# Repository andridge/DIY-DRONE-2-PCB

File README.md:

# DIY-DRONE-PCB

https://github.com/andridge/DIY-DRONE-PCB/assets/46260701/71bfbc1b-cc14-4874-8b07-093efc903e75

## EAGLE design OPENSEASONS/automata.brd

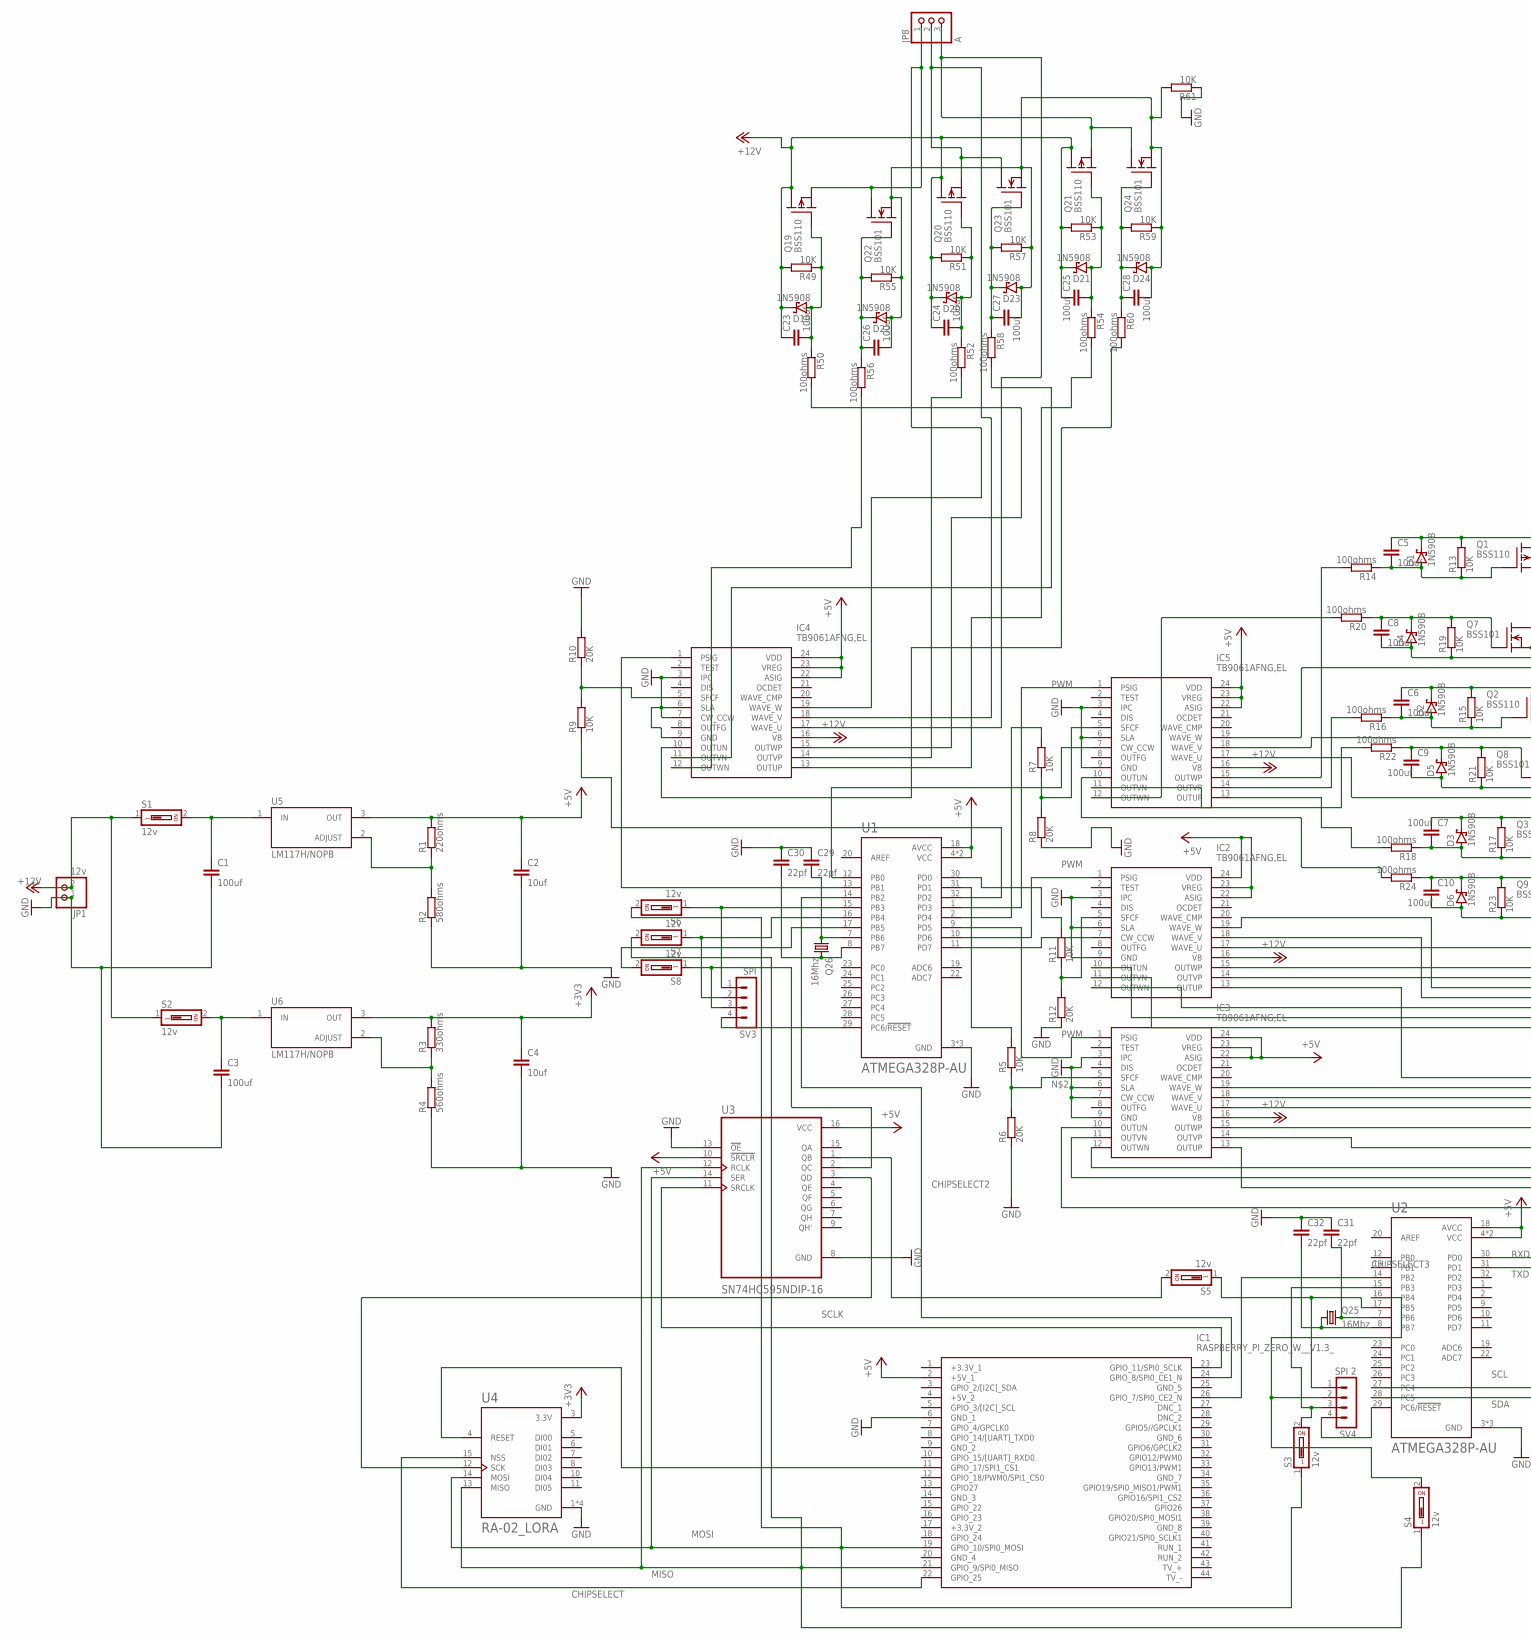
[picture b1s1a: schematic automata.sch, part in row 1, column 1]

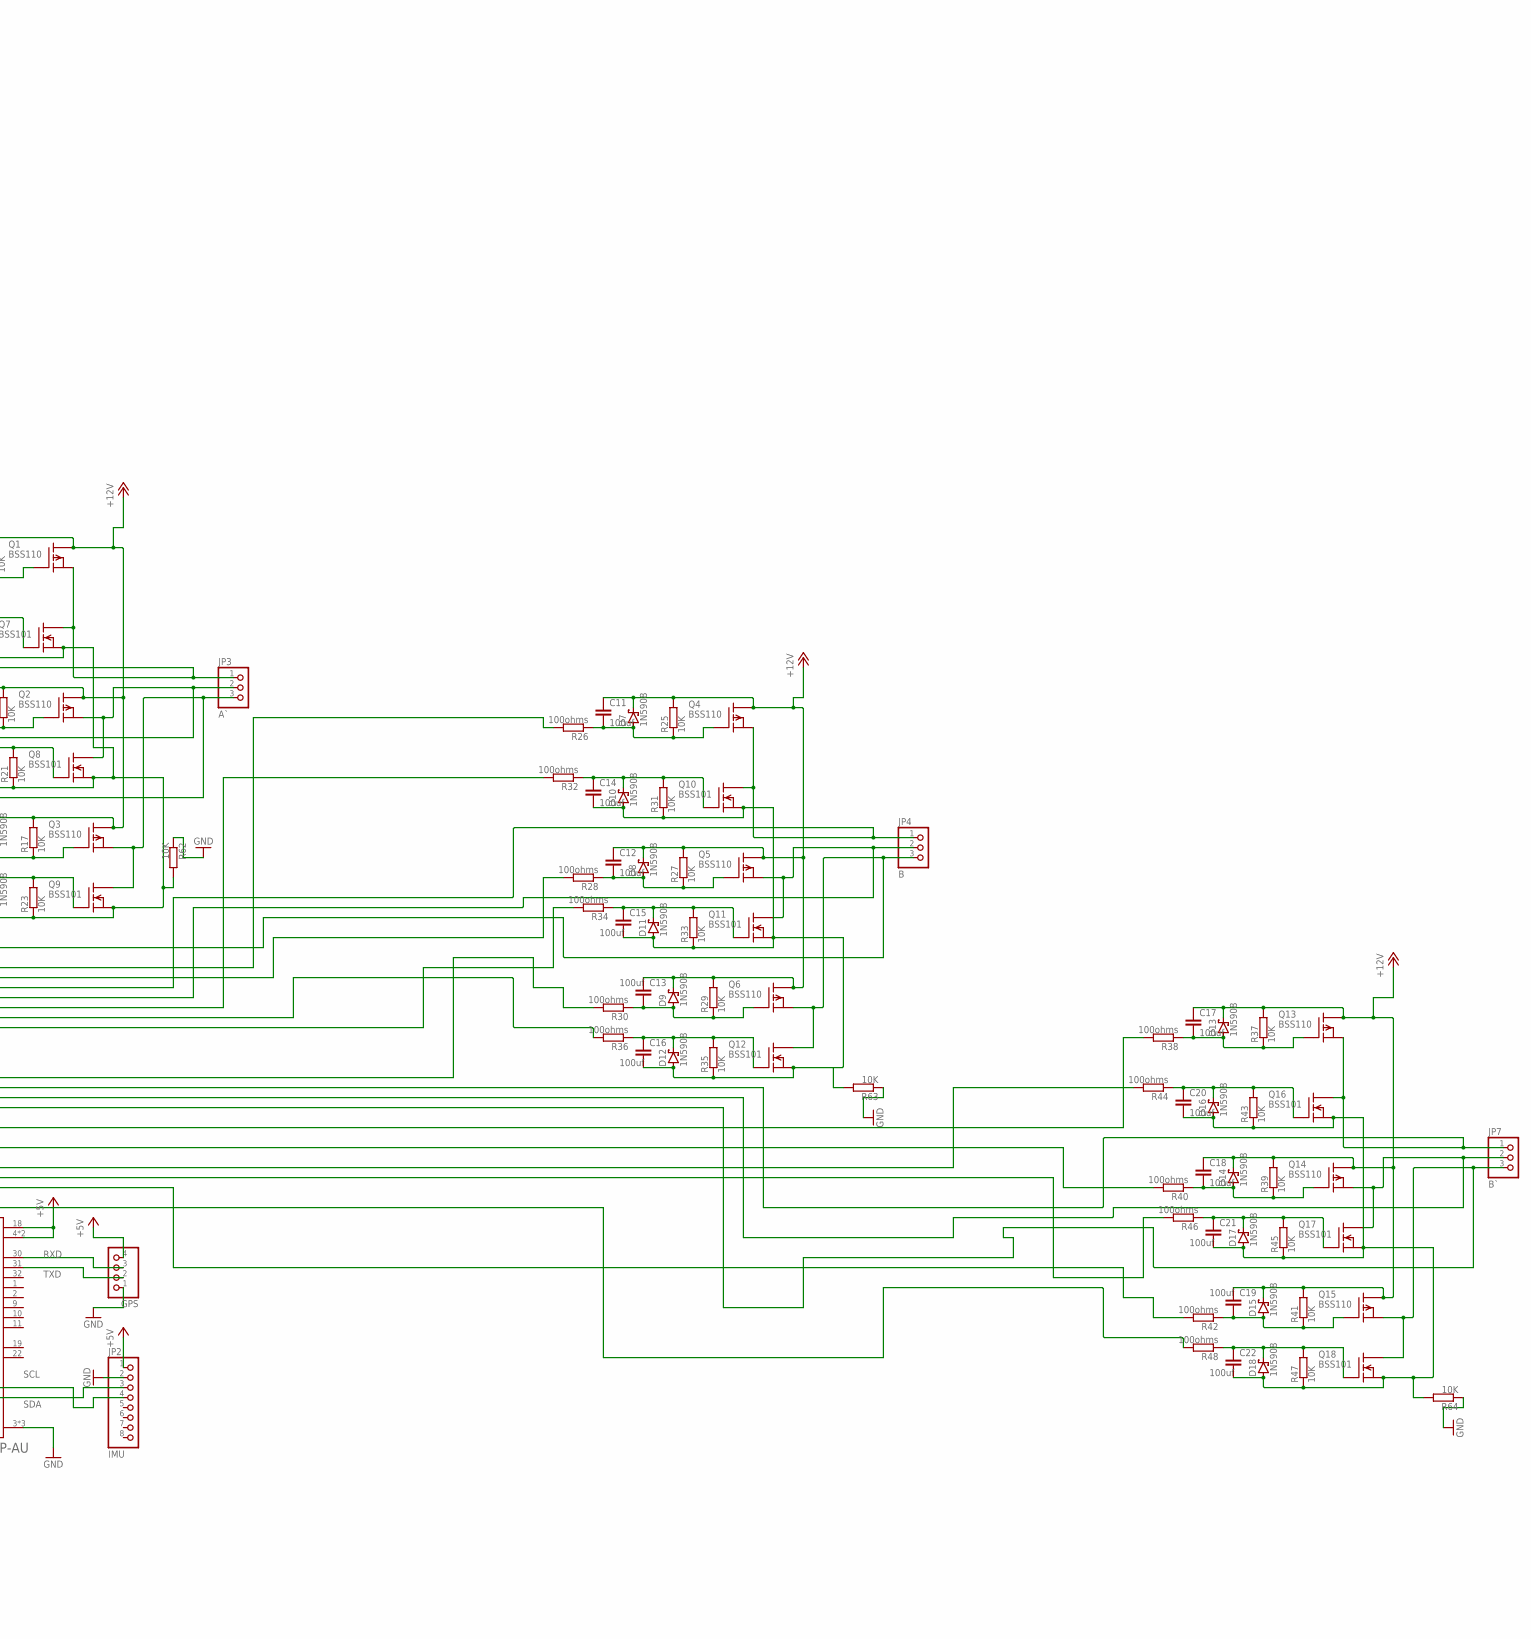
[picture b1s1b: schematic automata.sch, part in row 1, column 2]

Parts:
C1, C3, C5, C6, C7, C8, C9, C10, C11, C12, C13, C14, C15, C16, C17, C18, C19, C20, C21, C22, C23, C24, C25, C26, C27, C28: 100uf; C0402K
C2, C4: 10uf; C0402K
C29, C30, C31, C32: 22pf; C0402K
D1, D2, D3, D4, D5, D6, D7, D8, D9, D10, D11, D12, D13, D14, D15, D16, D17, D18, D19, D20, D21, D22, D23, D24: 1N5908; C4111-15
GPS: PINHD-1X4; 1X04
IC1: RASPBERRY_PI_ZERO_W__V1.3_; RASPBERRYPIZEROWV13
IC2, IC3, IC4, IC5: TB9061AFNG,EL; SOP65P760X160-24N
JP1: 12v; 1X02
JP2: IMU; 1X08
JP3: A`; 1X03
JP4: B; 1X03
JP7: B`; 1X03
JP8: A; 1X03
Q1, Q2, Q3, Q4, Q5, Q6, Q13, Q14, Q15, Q19, Q20, Q21: BSS110; TO92
Q7, Q8, Q9, Q10, Q11, Q12, Q16, Q17, Q18, Q22, Q23, Q24: BSS101; TO92
Q25, Q26: 16Mhz; HC49/S
R1: 220ohms; SMK
R2: 580ohms; SMK
R3: 330ohms; SMK
R4: 560ohms; SMK
R5, R7, R9, R11, R13, R15, R17, R19, R21, R23, R25, R27, R29, R31, R33, R35, R37, R39, R41, R43, R45, R47, R49, R51, R53, R55, R57, R59, R61, R62, R63, R64: 10K; SMK
R6, R8, R10, R12: 20K; SMK
R14, R16, R18, R20, R22, R24, R26, R28, R30, R32, R34, R36, R38, R40, R42, R44, R46, R48, R50, R52, R54, R56, R58, R60: 100ohms; SMK
S1, S2, S3, S4, S5, S6, S7, S8: 12v; DS-01
SV3: SPI; MA04-1
SV4: SPI 2; MA04-1
U1, U2: ATMEGA328P-AU; QFP80P900X900X120-32N
U3: SN74HC595NDIP-16; DIP794W45P254L1969H508Q16
U4: RA-02_LORA; MODULE_RA-02_LORA
U5, U6: LM117H/NOPB; TO254P914H670-3

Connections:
+3V3: C4.1, R3.1, U4.3 (3.3V), U6.3 (OUT)
+5V: C2.1, GPS.4, IC1.2 (+5V_1), IC2.22 (ASIG), IC2.23 (VREG), IC2.24 (VDD), IC3.22 (ASIG), IC3.23 (VREG), IC3.24 (VDD), IC4.22 (ASIG), IC4.23 (VREG), IC4.24 (VDD), IC5.22 (ASIG), IC5.23 (VREG), IC5.24 (VDD), JP2.1, R1.1, U1.4 (VCC), U1.6 (VCC), U1.18 (AVCC), U2.4 (VCC), U2.6 (VCC), U2.18 (AVCC), U3.10 (!SRCLR), U3.16 (VCC), U5.3 (OUT)
+12V: C5.1, C6.1, C7.1, C11.1, C12.1, C13.1, C17.1, C18.1, C19.1, C23.1, C24.1, C25.1, D1.C, D2.C, D3.C, D7.C, D8.C, D9.C, D13.C, D14.C, D15.C, D19.C, D20.C, D21.C, IC2.16 (VB), IC3.16 (VB), IC4.16 (VB), IC5.16 (VB), JP1.2, Q1.3 (D), Q2.3 (D), Q3.3 (D), Q4.3 (D), Q5.3 (D), Q6.3 (D), Q13.3 (D), Q14.3 (D), Q15.3 (D), Q19.3 (D), Q20.3 (D), Q21.3 (D), R13.1, R15.1, R17.1, R25.1, R27.1, R29.1, R37.1, R39.1, R41.1, R49.1, R51.1, R53.1, S1.1, S2.1
CHIPSELECT: IC1.22 (GPIO_25), U4.15 (NSS)
CHIPSELECT2: IC1.24 (GPIO_8/SPI0_CE1_N), U1.14 (PB2)
CHIPSELECT3: IC1.26 (GPIO_7/SPI0_CE2_N), U2.14 (PB2)
GND: C1.2, C2.2, C3.2, C4.2, C29.1, C30.1, C31.1, C32.1, GPS.1, IC1.6 (GND_1), IC2.3 (IPC), IC2.6 (SLA), IC2.9 (GND), IC3.3 (IPC), IC3.6 (SLA), IC3.7 (CW_CCW), IC3.9 (GND), IC4.3 (IPC), IC4.6 (SLA), IC4.7 (CW_CCW), IC4.9 (GND), IC5.3 (IPC), IC5.6 (SLA), IC5.9 (GND), JP1.1, JP2.2, R2.2, R4.2, R6.2, R8.2, R10.1, R12.2, R61.2, R62.2, R63.2, R64.2, U1.3 (GND), U1.5 (GND), U1.21 (GND), U2.3 (GND), U2.5 (GND), U2.21 (GND), U3.8 (GND), U3.13 (!OE), U4.1 (GND), U4.2 (GND), U4.9 (GND), U4.16 (GND)
MISO: IC1.21 (GPIO_9/SPI0_MISO), S4.1, S7.2, U3.12 (RCLK), U4.13 (MISO)
MOSI: IC1.19 (GPIO_10/SPI0_MOSI), S3.1, S6.2, U3.14 (SER), U4.14 (MOSI)
unnamed: C1.1, S1.2, U5.1 (IN)
unnamed: IC3.5 (SFCF), R5.2, R6.1
unnamed: IC5.5 (SFCF), R7.2, R8.1
unnamed: IC3.1 (PSIG), U1.9 (PD5)
unnamed: R1.2, R2.1, U5.2 (ADJUST)
unnamed: R5.1, U1.31 (PD1)
unnamed: C3.1, S2.2, U6.1 (IN)
unnamed: IC4.1 (PSIG), U1.13 (PB1)
unnamed: R9.2, U1.32 (PD2)
unnamed: R7.1, U1.2 (PD4)
unnamed: R3.2, R4.1, U6.2 (ADJUST)
unnamed: IC5.1 (PSIG), U1.1 (PD3)
unnamed: IC2.5 (SFCF), R11.2, R12.1
unnamed: IC4.5 (SFCF), R9.1, R10.2
unnamed: C5.2, D1.A, Q1.2 (G), R13.2, R14.2
unnamed: U3.3 (QD), U4.12 (SCK)
unnamed: S8.1, SV3.3, U3.2 (QC)
unnamed: S5.2, U3.1 (QB)
unnamed: IC2.7 (CW_CCW), U1.11 (PD7)
unnamed: IC5.7 (CW_CCW), U1.12 (PB0)
unnamed: C26.2, C27.2, C28.2, D22.A, D23.A, D24.A, Q22.1 (S), Q23.1 (S), Q24.1 (S), R55.2, R57.2, R59.2, R61.1
unnamed: IC5.15 (OUTWP), R14.1
unnamed: IC5.19 (WAVE_W), JP3.1, Q1.1 (S), Q7.3 (D)
unnamed: C6.2, D2.A, Q2.2 (G), R15.2, R16.2
unnamed: C11.2, D7.A, Q4.2 (G), R25.2, R26.2
unnamed: IC5.14 (OUTVP), R16.1
unnamed: C7.2, D3.A, Q3.2 (G), R17.2, R18.2
unnamed: C14.2, C15.2, C16.2, D10.A, D11.A, D12.A, Q10.1 (S), Q11.1 (S), Q12.1 (S), R31.2, R33.2, R35.2, R63.1
unnamed: IC5.13 (OUTUP), R18.1
unnamed: IC5.18 (WAVE_V), JP3.2, Q2.1 (S), Q8.3 (D)
unnamed: C10.1, D6.C, Q9.2 (G), R23.1, R24.2
unnamed: IC2.15 (OUTWP), R26.1
unnamed: C8.1, D4.C, Q7.2 (G), R19.1, R20.2
unnamed: IC5.12 (OUTWN), R20.1
unnamed: IC2.19 (WAVE_W), JP4.1, Q4.1 (S), Q10.3 (D)
unnamed: C9.1, D5.C, Q8.2 (G), R21.1, R22.2
unnamed: IC5.11 (OUTVN), R22.1
unnamed: C12.2, D8.A, Q5.2 (G), R27.2, R28.2
unnamed: IC2.14 (OUTVP), R28.1
unnamed: IC5.10 (OUTUN), R24.1
unnamed: C29.2, Q26.1, U1.7 (PB6)
unnamed: C13.2, D9.A, Q6.2 (G), R29.2, R30.2
unnamed: IC2.13 (OUTUP), R30.1
unnamed: IC5.17 (WAVE_U), JP3.3, Q3.1 (S), Q9.3 (D)
unnamed: IC2.18 (WAVE_V), JP4.2, Q5.1 (S), Q11.3 (D)
unnamed: C14.1, D10.C, Q10.2 (G), R31.1, R32.2
unnamed: C15.1, D11.C, Q11.2 (G), R33.1, R34.2
unnamed: IC2.11 (OUTVN), R34.1
unnamed: IC2.10 (OUTUN), R36.1
unnamed: C16.1, D12.C, Q12.2 (G), R35.1, R36.2
unnamed: C30.2, Q26.2, U1.8 (PB7)
unnamed: IC3.12 (OUTWN), R44.1
unnamed: IC2.17 (WAVE_U), JP4.3, Q6.1 (S), Q12.3 (D)
unnamed: C17.2, D13.A, Q13.2 (G), R37.2, R38.2
unnamed: C8.2, C9.2, C10.2, D4.A, D5.A, D6.A, Q7.1 (S), Q8.1 (S), Q9.1 (S), R19.2, R21.2, R23.2, R62.1
unnamed: IC3.15 (OUTWP), R38.1
unnamed: IC3.19 (WAVE_W), JP7.1, Q13.1 (S), Q16.3 (D)
unnamed: C18.2, D14.A, Q14.2 (G), R39.2, R40.2
unnamed: IC3.14 (OUTVP), R40.1
unnamed: C19.2, D15.A, Q15.2 (G), R41.2, R42.2
unnamed: IC3.11 (OUTVN), R46.1
unnamed: IC3.18 (WAVE_V), JP7.2, Q14.1 (S), Q17.3 (D)
unnamed: C20.1, D16.C, Q16.2 (G), R43.1, R44.2
unnamed: C21.1, D17.C, Q17.2 (G), R45.1, R46.2
unnamed: S5.1, SV4.1, U2.17 (PB5)
unnamed: IC3.10 (OUTUN), R48.1
unnamed: C22.1, D18.C, Q18.2 (G), R47.1, R48.2
unnamed: SV3.4, U1.29 (PC6/!RESET)
unnamed: IC4.12 (OUTWN), R56.1
unnamed: IC3.17 (WAVE_U), JP7.3, Q15.1 (S), Q18.3 (D)
unnamed: C23.2, D19.A, Q19.2 (G), R49.2, R50.2
unnamed: C20.2, C21.2, C22.2, D16.A, D17.A, D18.A, Q16.1 (S), Q17.1 (S), Q18.1 (S), R43.2, R45.2, R47.2, R64.1
unnamed: IC4.15 (OUTWP), R50.1
unnamed: IC4.19 (WAVE_W), JP8.1, Q19.1 (S), Q22.3 (D)
unnamed: C24.2, D20.A, Q20.2 (G), R51.2, R52.2
unnamed: IC4.14 (OUTVP), R52.1
unnamed: C25.2, D21.A, Q21.2 (G), R53.2, R54.2
unnamed: IC4.13 (OUTUP), R54.1
unnamed: IC4.18 (WAVE_V), JP8.2, Q20.1 (S), Q23.3 (D)
unnamed: C26.1, D22.C, Q22.2 (G), R55.1, R56.2
unnamed: C27.1, D23.C, Q23.2 (G), R57.1, R58.2
unnamed: IC4.11 (OUTVN), R58.1
unnamed: IC4.10 (OUTUN), R60.1
unnamed: C28.1, D24.C, Q24.2 (G), R59.1, R60.2
unnamed: C31.2, Q25.2, U2.7 (PB6)
unnamed: C32.2, Q25.1, U2.8 (PB7)
unnamed: IC4.17 (WAVE_U), JP8.3, Q21.1 (S), Q24.3 (D)
unnamed: IC2.12 (OUTWN), R32.1
unnamed: S4.2, SV4.2, U2.16 (PB4)
unnamed: IC3.13 (OUTUP), R42.1
unnamed: S6.1, SV3.1, U1.15 (PB3)
unnamed: S7.1, SV3.2, U1.16 (PB4)
unnamed: S8.2, U1.17 (PB5)
unnamed: IC1.11 (GPIO_17/SPI1_CS1), U4.4 (RESET)
unnamed: S3.2, SV4.3, U2.15 (PB3)
unnamed: SV4.4, U2.29 (PC6/!RESET)
PWM: IC2.1 (PSIG), U1.10 (PD6)
RPM: R11.1, U1.30 (PD0)
RXD: GPS.3, U2.30 (PD0)
SCL: JP2.4, U2.27 (PC4)
SCLK: IC1.23 (GPIO_11/SPI0_SCLK), U3.11 (SRCLK)
SDA: JP2.3, U2.28 (PC5)
TXD: GPS.2, U2.31 (PD1)

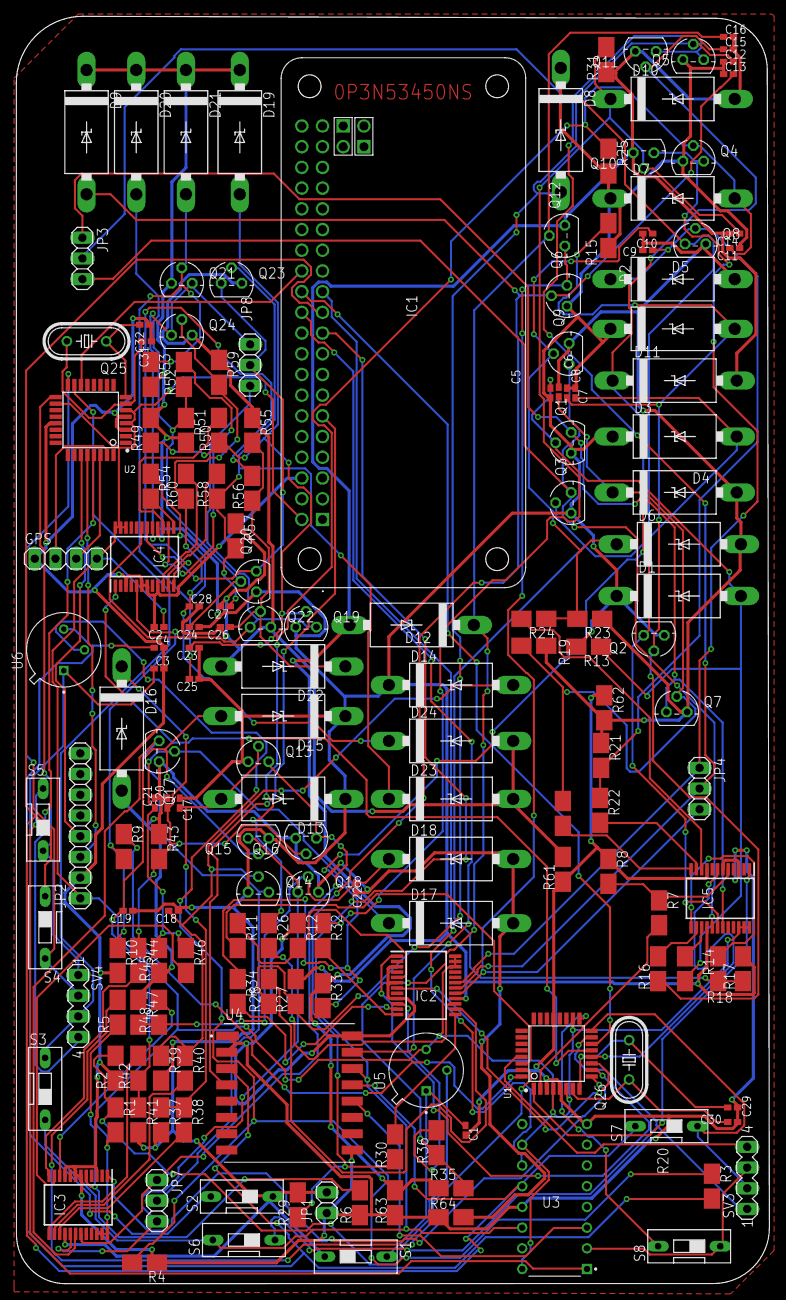
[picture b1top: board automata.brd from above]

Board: 2 copper layers, 92.4 x 155.5 mm, 174 parts (0 on the bottom side), 112 nets.
